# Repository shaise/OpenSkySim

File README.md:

# OpenSkySim
A wireless rc simulator controller

## Description
This open project aims to develop a small USB dongle that lets you use your FrSky transmitter as an RC simulator controller wirelessly. You only need to bind your transmitter to the dongle and start playing!  
This dongle supports both standard HID compatible simulators, AND PhoenixRC!  
The hardware is bases on STM32F103 microcontroller and TI CC2500 transceiver. The firmware is based on OpenSky FrSky-compatible receiver: https://github.com/fishpepper/OpenSky

## Assembling instructions

* Order the PCB by sending the [gerber files ](/Release/gerbers_frsim_2Layer_FR4.zip) to a manufacturer of your choice. I recommend [JLCPCB](https://jlcpcb.com/).
* Order all parts as listed in the [BOM](/Release/OpenSkySimBom.pdf) file. You will need a 0603 kit of resistors and capacitors, and for all other parts you will find a link in the BOM.
* Solder all parts. You can use the [Interactive BOM](https://htmlpreview.github.io/?https://github.com/shaise/OpenSkySim/blob/main/Hardware/Bom/Interactive_bom.html) to assist you. 
* For the transmitter module, I used one without built in antenna, So if you are using the same module, you will need to add an antenna by soldering a 0.5mm transformer wire to the antenna pin, then trim the wire to a length of 31.5mm. (I tried one module with on board antenna but the reception was bad, If you find one that works, please let me know). Plese note: there are parts on both side of the PC

Top Side (click to enlarge):  

* If you have an access to a 3D printer you can print a plastic enclosure. Download and print the 2 stl files in the  folder. Use different color for the first 3 layers to get a nice text effect. 

## Programming the firmware
* You will need an ST-Link V2 compatible programmer and programming cable (links in the BOM)
* From the JST cable and Dupont connector kit prepare the programming cable as shown in the image (Note the colors!):

* Connect the cable between the programmer and dongle:  
  
* Connect the Stlink programmer to the PC. (no need to connect the dongle, it is powered from the programmer)
* Download the OpenSkySim firmware, and use a programming software such as the  and programm the dongle.  

## Usage
This dongle works with FR-Sky telemetry compatible transmitters. (SW 1 and 2 off on DJT modules)  
You first need to bind the dongle with the transmitter (this is a one-time operation, repeat only if you change transmitter):  
* Press and hold the bind button and insert the dongle to the PC. Wait for the green light to turn on.

* Start binding procedure in your transmitter. If you are using an external module such as the DJT, Press and hold the module bind button and turn on the transmitter. 
* Wait for the red led on the dongle to start blinking. When it does, binding is complete! Turn off the transmitter and pull the dongle out from the PC.  

From now on all you need to do to use the simulator is just by using the slide switch, select the operation mode: either 'Std' for standard HID compatible simulator or 'Pnx' for PhoenixRC, then insert the dongle to the PC and start Simm-ing!

Remark: When using the dongle in 'Std' mode, the PC will recognize it as "OpenSky wireless sim dongle" HID game controller.

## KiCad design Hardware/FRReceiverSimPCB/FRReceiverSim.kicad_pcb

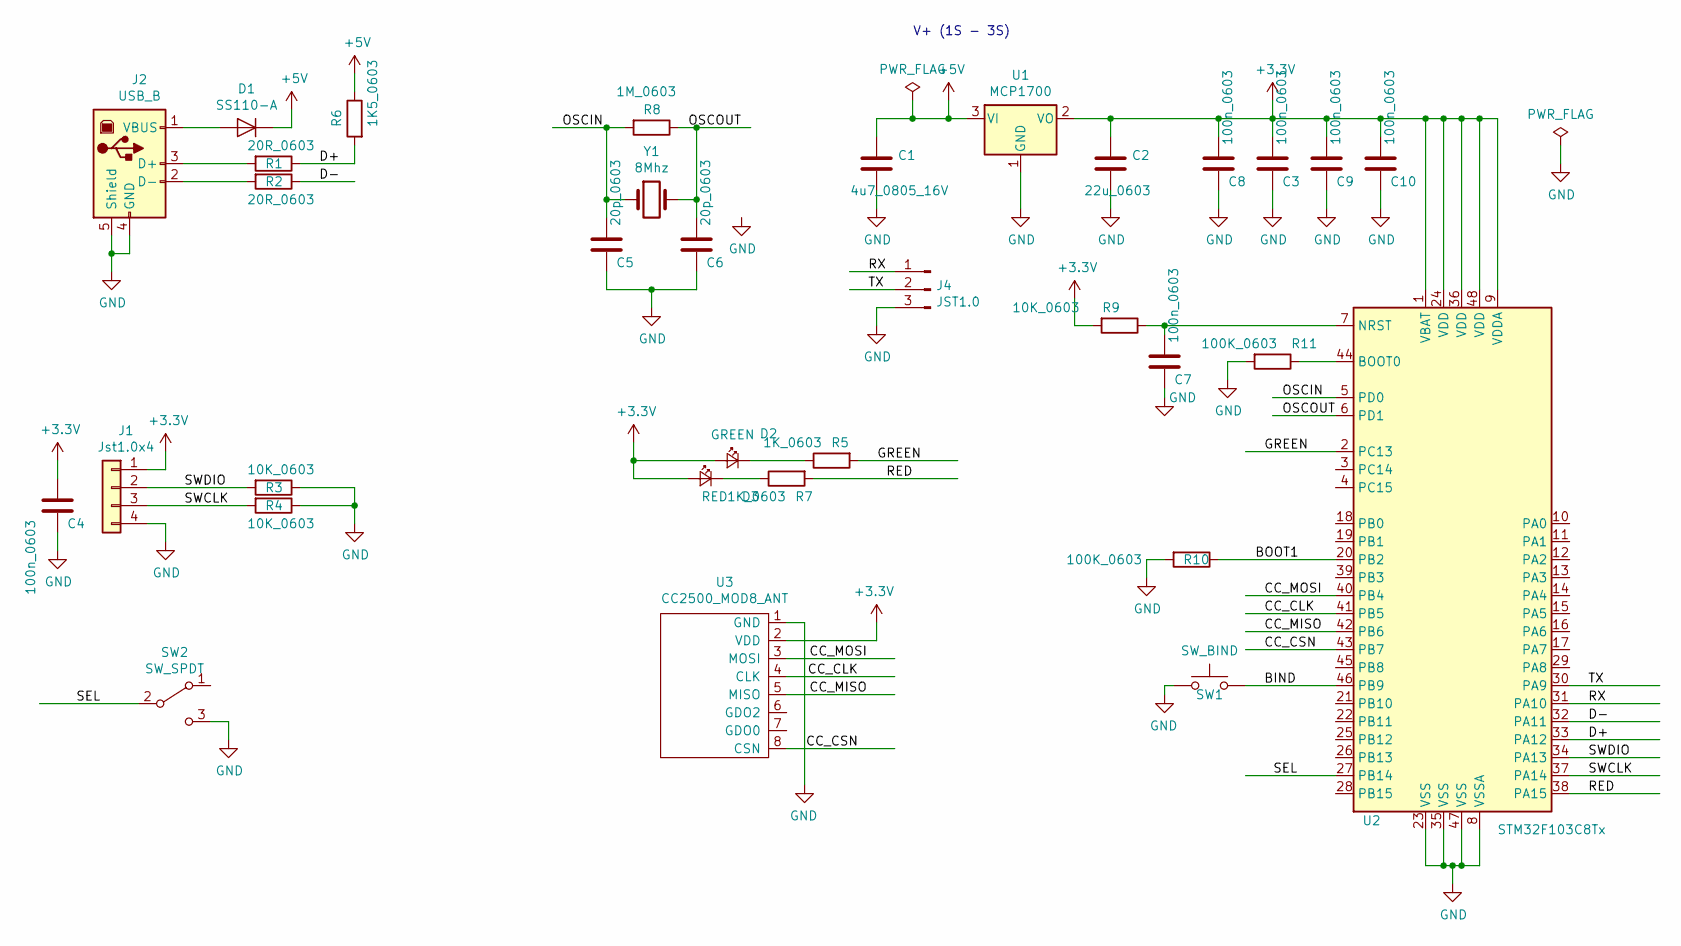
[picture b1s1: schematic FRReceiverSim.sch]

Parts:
C1: 4u7_0805_16V; C_0805_2012Metric
C2: 22u_0603; C_0603_1608Metric
C3, C4, C7, C8, C9, C10: 100n_0603; C_0603_1608Metric
C5, C6: 20p_0603; C_0603_1608Metric
D1: SS110-A; D_SMA
D2: GREEN; LED_0603_1608Metric
D3: RED; LED_0603_1608Metric
J1: Jst1.0x4; JST_SH_SM04B-SRSS-TB_1x04-1MP_P1.00mm_Horizontal
J2: USB_B; USB_A_CNCTech_1001-011-01101_Horizontal
J4: JST1.0; JST_SH_SM03B-SRSS-TB_1x03-1MP_P1.00mm_Horizontal
R1, R2: 20R_0603; R_0603_1608Metric
R3, R4, R9: 10K_0603; R_0603_1608Metric
R5, R7: 1K_0603; R_0603_1608Metric
R6: 1K5_0603; R_0603_1608Metric
R8: 1M_0603; R_0603_1608Metric
R10, R11: 100K_0603; R_0603_1608Metric
SW1: SW_BIND; SW_SPST_4x3
SW2: SW_SPDT; SW_SPDT_PCM12
U1: MCP1700; SOT-23
U2: STM32F103C8Tx; LQFP-48_7x7mm_P0.5mm
U3: CC2500_MOD8_ANT
Y1: 8Mhz; Crystal_SMD_HC49-SD

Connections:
+3V3: C2.1, C3.1, C4.1, C8.1, C9.1, C10.1, D2.2 (A), D3.2 (A), J1.1, R9.2, U1.2 (VO), U2.1 (VBAT), U2.9 (VDDA), U2.24 (VDD), U2.36 (VDD), U2.48 (VDD), U3.2 (VDD)
+5V: C1.1, D1.1 (K), R6.1, U1.3 (VI)
/BIND: SW1.1, U2.46 (PB9)
/BOOT1: R10.1, U2.20 (PB2)
/CC_CLK: U2.41 (PB5), U3.4 (CLK)
/CC_CSN: U2.43 (PB7), U3.8 (CSN)
/CC_MISO: U2.42 (PB6), U3.5 (MISO)
/CC_MOSI: U2.40 (PB4), U3.3 (MOSI)
/D+: R1.1, R6.2, U2.33 (PA12)
/D-: R2.1, U2.32 (PA11)
/GREEN: R5.2, U2.2 (PC13)
/OSCIN: C5.1, R8.2, U2.5 (PD0), Y1.1
/OSCOUT: C6.1, R8.1, U2.6 (PD1), Y1.2
/RED: R7.2, U2.38 (PA15)
/RX: J4.1, U2.31 (PA10)
/SEL: SW2.2 (B), U2.27 (PB14)
/SWCLK: J1.3, R4.2, U2.37 (PA14)
/SWDIO: J1.2, R3.2, U2.34 (PA13)
/TX: J4.2, U2.30 (PA9)
GND: C1.2, C2.2, C3.2, C4.2, C5.2, C6.2, C7.2, C8.2, C9.2, C10.2, J1.4, J2.4 (GND), J2.5 (Shield), J4.3, R3.1, R4.1, R10.2, R11.2, SW1.2, SW2.3 (C), U1.1 (GND), U2.8 (VSSA), U2.23 (VSS), U2.35 (VSS), U2.47 (VSS), U3.1 (GND)
unnamed: C7.1, R9.1, U2.7 (NRST)
unnamed: D1.2 (A), J2.1 (VBUS)
unnamed: D2.1 (K), R5.1
unnamed: D3.1 (K), R7.1
unnamed: J2.2 (D-), R2.2
unnamed: J2.3 (D+), R1.2
unnamed: R11.1, U2.44 (BOOT0)

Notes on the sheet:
V+ (1S - 3S)

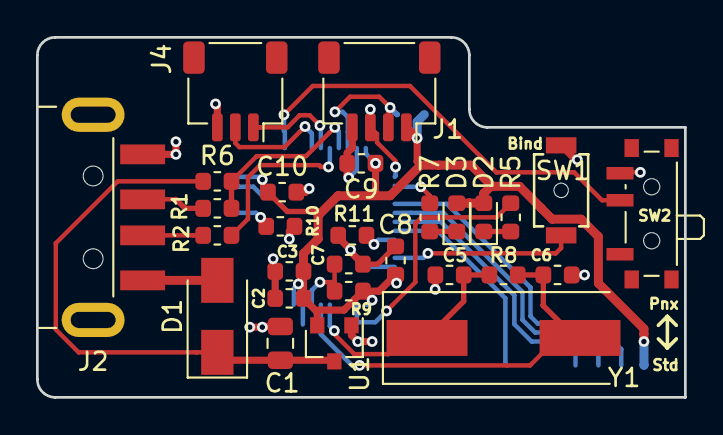
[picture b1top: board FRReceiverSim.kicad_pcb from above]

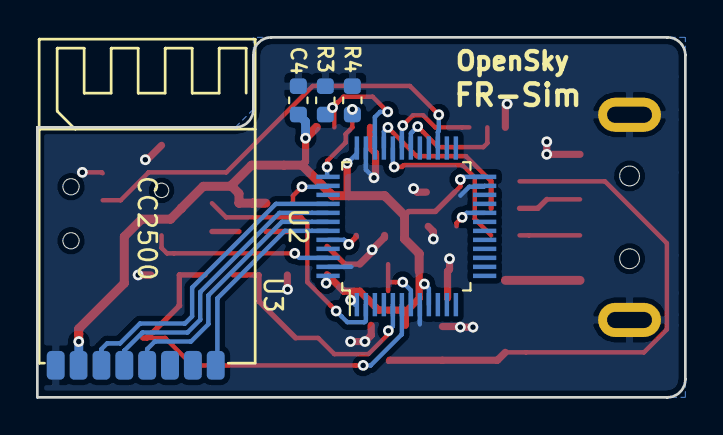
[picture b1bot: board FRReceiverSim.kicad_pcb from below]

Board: 2 copper layers, 36.0 x 20.0 mm, 33 parts (5 on the bottom side), 27 nets.

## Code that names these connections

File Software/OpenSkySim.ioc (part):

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Mcu.Name=STM32F103C(8-B)Tx
Mcu.Package=LQFP48
Mcu.UserName=STM32F103C8Tx
PA10.Mode=Asynchronous
PA10.Signal=USART1_RX
PA11.Mode=Device
PA11.Signal=USB_DM
PA12.Mode=Device
PA12.Signal=USB_DP
PA13.Mode=Serial_Wire
PA13.Signal=SYS_JTMS-SWDIO
PA14.Mode=Serial_Wire
PA14.Signal=SYS_JTCK-SWCLK
PA15.GPIOParameters=GPIO_Label
PA15.GPIO_Label=RED_LED
PA15.Signal=GPIO_Output
PA9.Mode=Asynchronous
PA9.Signal=USART1_TX
PB14.GPIOParameters=GPIO_PuPd,GPIO_Label
PB14.GPIO_Label=PNX_SEL
PB14.GPIO_PuPd=GPIO_PULLUP
PB14.Signal=GPIO_Input
PB4.GPIOParameters=GPIO_Speed,GPIO_Label
PB4.GPIO_Label=CC2500_MOSI
PB4.GPIO_Speed=GPIO_SPEED_FREQ_LOW
PB4.Signal=GPIO_Output
PB5.GPIOParameters=GPIO_Label
PB5.GPIO_Label=CC2500_CLK
PB5.Signal=GPIO_Output
PB6.GPIOParameters=GPIO_PuPd,GPIO_Label
PB6.GPIO_Label=CC2500_MISO
PB6.GPIO_PuPd=GPIO_PULLUP
PB6.Signal=GPIO_Input
PB7.GPIOParameters=GPIO_Label
PB7.GPIO_Label=CC2500_CSN
PB7.Signal=GPIO_Output
PB9.GPIOParameters=GPIO_PuPd,GPIO_Label
PB9.GPIO_Label=BIND
PB9.GPIO_PuPd=GPIO_PULLUP
PB9.Signal=GPIO_Input
PC13-TAMPER-RTC.GPIOParameters=PinState,GPIO_Label
PC13-TAMPER-RTC.GPIO_Label=ONBOARD_LED
PC13-TAMPER-RTC.PinState=GPIO_PIN_SET
PC13-TAMPER-RTC.Signal=GPIO_Output
PD0-OSC_IN.Mode=HSE-External-Oscillator
PD0-OSC_IN.Signal=RCC_OSC_IN
PD1-OSC_OUT.Mode=HSE-External-Oscillator
PD1-OSC_OUT.Signal=RCC_OSC_OUT
RCC.SYSCLKFreq_VALUE=72000000
RCC.SYSCLKSource=RCC_SYSCLKSOURCE_PLLCLK
board=ppm_stick

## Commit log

2021-01-31 initial working version
2021-01-31 add hardware and release files
2021-01-31 move README.md
2021-01-31 add image
2021-01-31 add images
2021-01-31 Add initial instructions
